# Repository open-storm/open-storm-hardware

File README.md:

# open-storm-hardware
Schematics for open storm hardware.

## perfect cell
**[perfect-cell]** contains Eagle schematics for the _perfect-cell_ board. This board is intended for use with the [perfect-cell](https://github.com/open-storm/perfect-cell) firmware. This board features:

- Cypress CY8C5888LTI-LP097 Programmable System-on-Chip
- Cortex M3 32-bit ARM processor
- 64 KB SRAM
- 256 KB Flash
- Support for Telit cellular modules
- 40 I/O pins for sensors and actuators

## level shifter and relay board
**[level-shifter]** contains Eagle schematics for a level shifter and relay board that can be used to interface the _perfect-cell_ board with higher voltage equipment (such as a valve or autosampler).

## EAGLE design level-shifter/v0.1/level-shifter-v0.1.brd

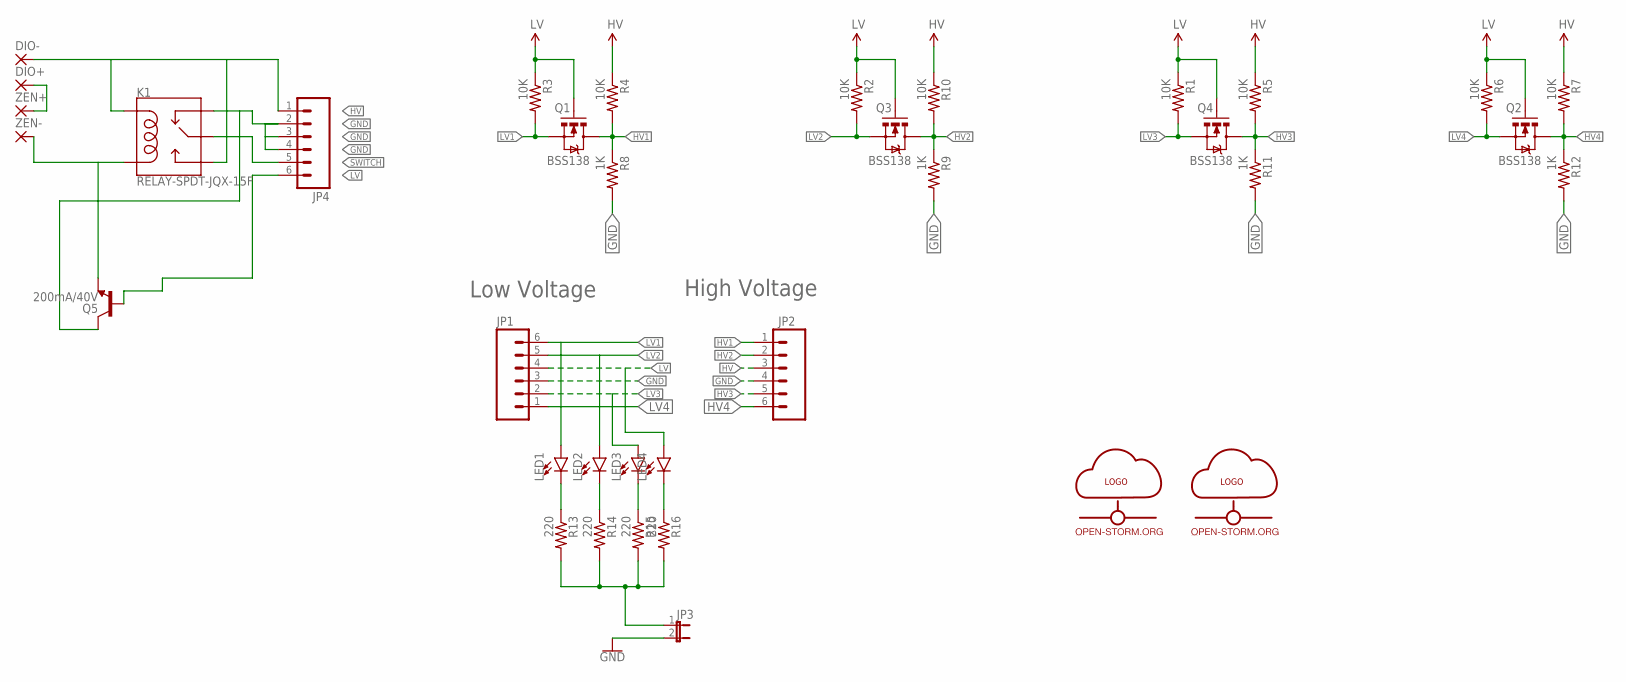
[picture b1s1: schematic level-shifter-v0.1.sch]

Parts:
DIO+: 2,15/1,0
DIO-: 2,15/1,0
JP1, JP2, JP4: M06SIP; 1X06
JP3: JUMPER-2PTH; 1X02
K1: RELAY-SPDT-JQX-15F; RELAY-T90
LED1, LED2, LED3, LED4: LED5MM; LED_5MM
Q1, Q2, Q3, Q4: BSS138; TO-92
Q5: 200mA/40V; TO-92
R1, R2, R3, R4, R5, R6, R7, R10: 10K; AXIAL-0.4
R8, R9, R11, R12: 1K; AXIAL-0.4
R13, R14, R15, R16: 220; AXIAL-0.4
U$1: OPEN-STORM-LOGO
U$2: OPEN-STORM-LOGO-SMALL
ZEN+: 2,15/1,0
ZEN-: 2,15/1,0

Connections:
GND: JP1.3, JP2.4, JP3.2, JP4.2, JP4.3, JP4.4, K1.NC, Q5.3 (C), R8.P$2 (2), R9.P$2 (2), R11.P$2 (2), R12.P$2 (2)
HV: DIO-.1, JP2.3, JP4.1, K1.COIL1, K1.NO, R4.P$1 (1), R5.P$1 (1), R7.P$1 (1), R10.P$1 (1)
HV1: JP2.1, Q1.1 (D), R4.P$2 (2), R8.P$1 (1)
HV2: JP2.2, Q3.1 (D), R9.P$1 (1), R10.P$2 (2)
HV3: JP2.5, Q4.1 (D), R5.P$2 (2), R11.P$1 (1)
HV4: JP2.6, Q2.1 (D), R7.P$2 (2), R12.P$1 (1)
LV: JP1.4, JP4.6, LED4.A, Q1.3 (G), Q2.3 (G), Q3.3 (G), Q4.3 (G), Q5.2 (B), R1.P$1 (1), R2.P$1 (1), R3.P$1 (1), R6.P$1 (1)
LV1: JP1.6, LED1.A, Q1.2 (S), R3.P$2 (2)
LV2: JP1.5, LED2.A, Q3.2 (S), R2.P$2 (2)
LV3: JP1.2, LED3.A, Q4.2 (S), R1.P$2 (2)
LV4: JP1.1, Q2.2 (S), R6.P$2 (2)
unnamed: DIO+.1, ZEN+.1
unnamed: LED4.K (C), R16.P$1 (1)
unnamed: LED2.K (C), R14.P$1 (1)
unnamed: K1.COIL2, Q5.1 (E), ZEN-.1
unnamed: LED1.K (C), R13.P$1 (1)
unnamed: LED3.K (C), R15.P$1 (1)
unnamed: JP3.1, R13.P$2 (2), R14.P$2 (2), R15.P$2 (2), R16.P$2 (2)
SWITCH: JP4.5, K1.MAIN

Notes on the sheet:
High Voltage
Low Voltage

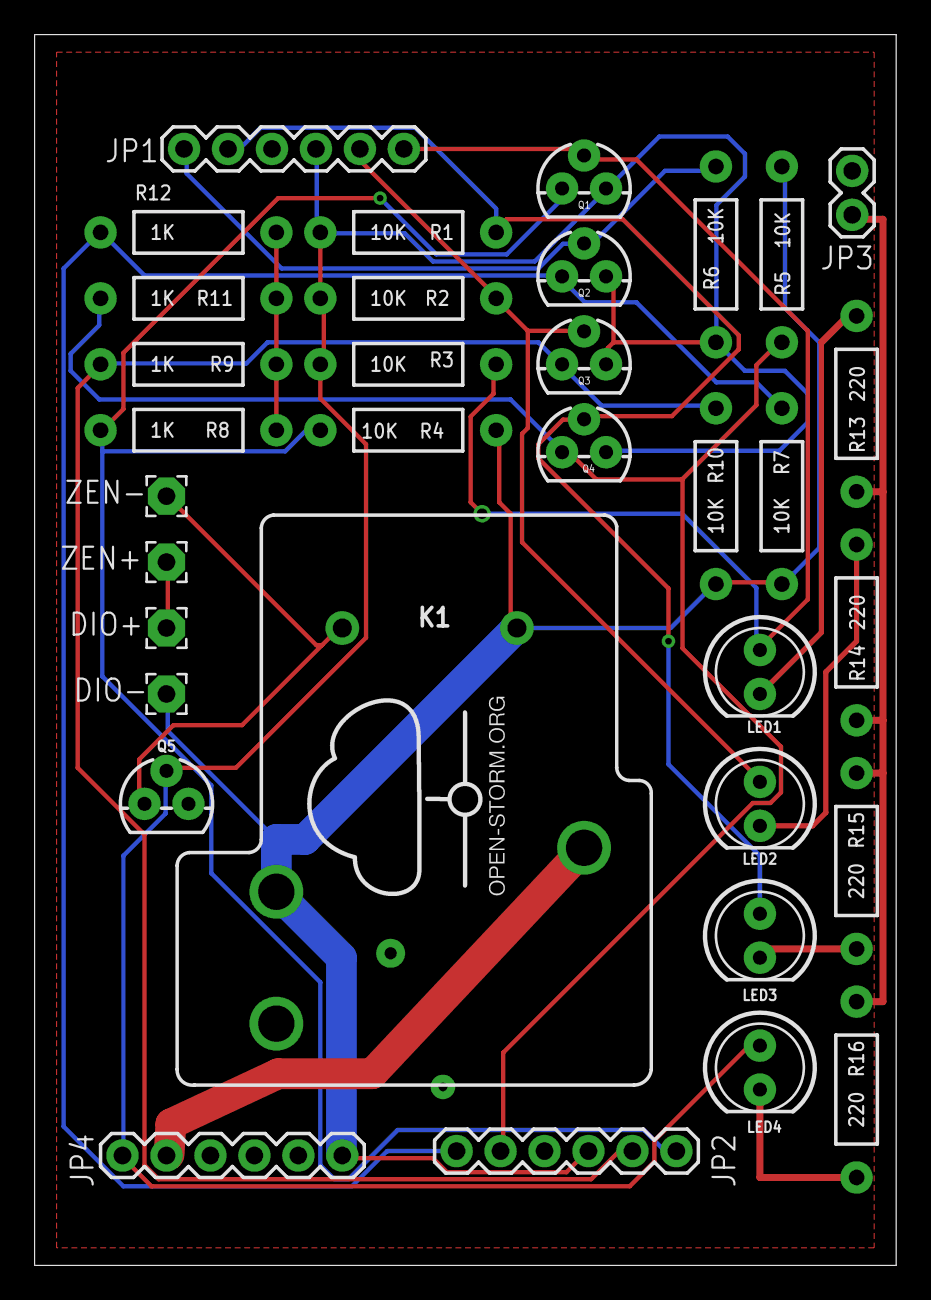
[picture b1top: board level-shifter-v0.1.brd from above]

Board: 2 copper layers, 49.8 x 71.1 mm, 36 parts (1 on the bottom side), 19 nets.

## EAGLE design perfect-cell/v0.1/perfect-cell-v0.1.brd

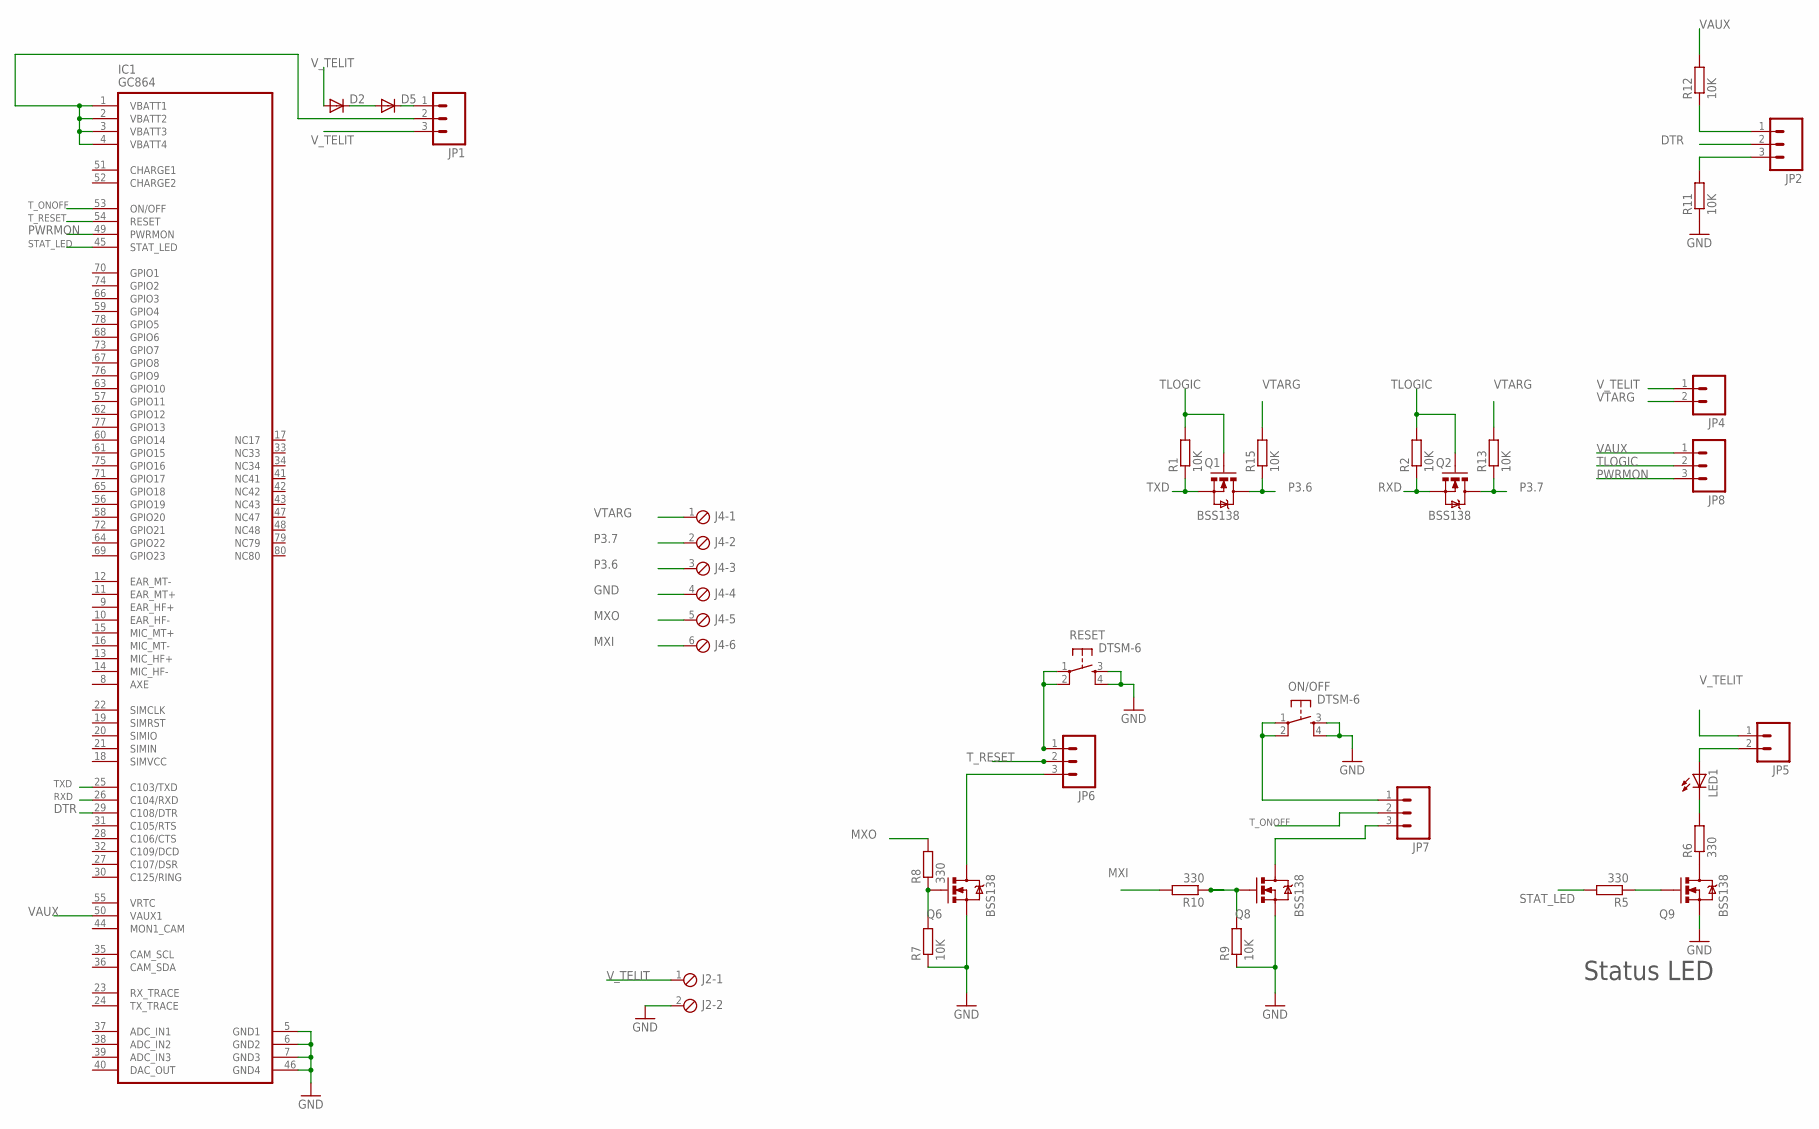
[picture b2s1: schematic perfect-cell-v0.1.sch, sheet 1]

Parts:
D2, D5: DIODESMA; SMA-DIODE
IC1: GC864
J2: MPT2; 2POL254
J4: MPT6; 6POL254
JP1, JP2, JP6, JP7, JP8: M03LOCK; 1X03_LOCK
JP4, JP5: M02LOCK; 1X02_LOCK
LED1: LEDSML0805; SML0805
ON/OFF: DTSM-6
Q1, Q2, Q6, Q8, Q9: BSS138; SOT23-3
R1, R2, R7, R9, R11, R12, R13, R15: 10K; R0805
R5, R6, R8, R10: 330; R0805
RESET: DTSM-6

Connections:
CHARGE1: IC1.51 (CHARGE1)
CHARGE2: IC1.52 (CHARGE2)
DTR: IC1.29 (C108/DTR), JP2.2
GND: IC1.5 (GND1), IC1.6 (GND2), IC1.7 (GND3), IC1.46 (GND4), J2.2, J4.4, ON/OFF.3, ON/OFF.4, Q6.2 (S), Q8.2 (S), Q9.2 (S), R7.1, R9.1, R11.1, RESET.3, RESET.4; also elsewhere on the board
MXI: J4.6, R10.2; also elsewhere on the board
MXO: J4.5, R8.2; also elsewhere on the board
unnamed: Q6.1 (G), R7.2, R8.1
unnamed: IC1.1 (VBATT1), IC1.2 (VBATT2), IC1.3 (VBATT3), IC1.4 (VBATT4), JP1.2
unnamed: D2.C, D5.A
unnamed: Q9.3 (D), R6.1
unnamed: JP5.2, LED1.A
unnamed: LED1.C, R6.2
unnamed: Q8.1 (G), R9.2, R10.1
unnamed: Q9.1 (G), R5.1
unnamed: JP2.1, R12.1
unnamed: JP2.3, R11.2
unnamed: D5.C, JP1.1
unnamed: JP7.3, Q8.3 (D)
unnamed: JP6.3, Q6.3 (D)
unnamed: JP7.1, ON/OFF.1, ON/OFF.2
unnamed: JP6.1, RESET.1, RESET.2
P3.6: J4.3, Q1.3 (D), R15.1; also elsewhere on the board
P3.7: J4.2, Q2.3 (D), R13.1; also elsewhere on the board
PWRMON: IC1.49 (PWRMON), JP8.3
RXD: IC1.26 (C104/RXD), Q2.2 (S), R2.1
STAT_LED: IC1.45 (STAT_LED), R5.2
TLOGIC: JP8.2, Q1.1 (G), Q2.1 (G), R1.2, R2.2
TXD: IC1.25 (C103/TXD), Q1.2 (S), R1.1
T_ONOFF: IC1.53 (ON/OFF), JP7.2
T_RESET: IC1.54 (RESET), JP6.2
VAUX: IC1.50 (VAUX1), JP8.1, R12.2
VTARG: J4.1, JP4.2, R13.2, R15.2
V_TELIT: D2.A, J2.1, JP1.3, JP4.1, JP5.1; also elsewhere on the board

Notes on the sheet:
Status LED

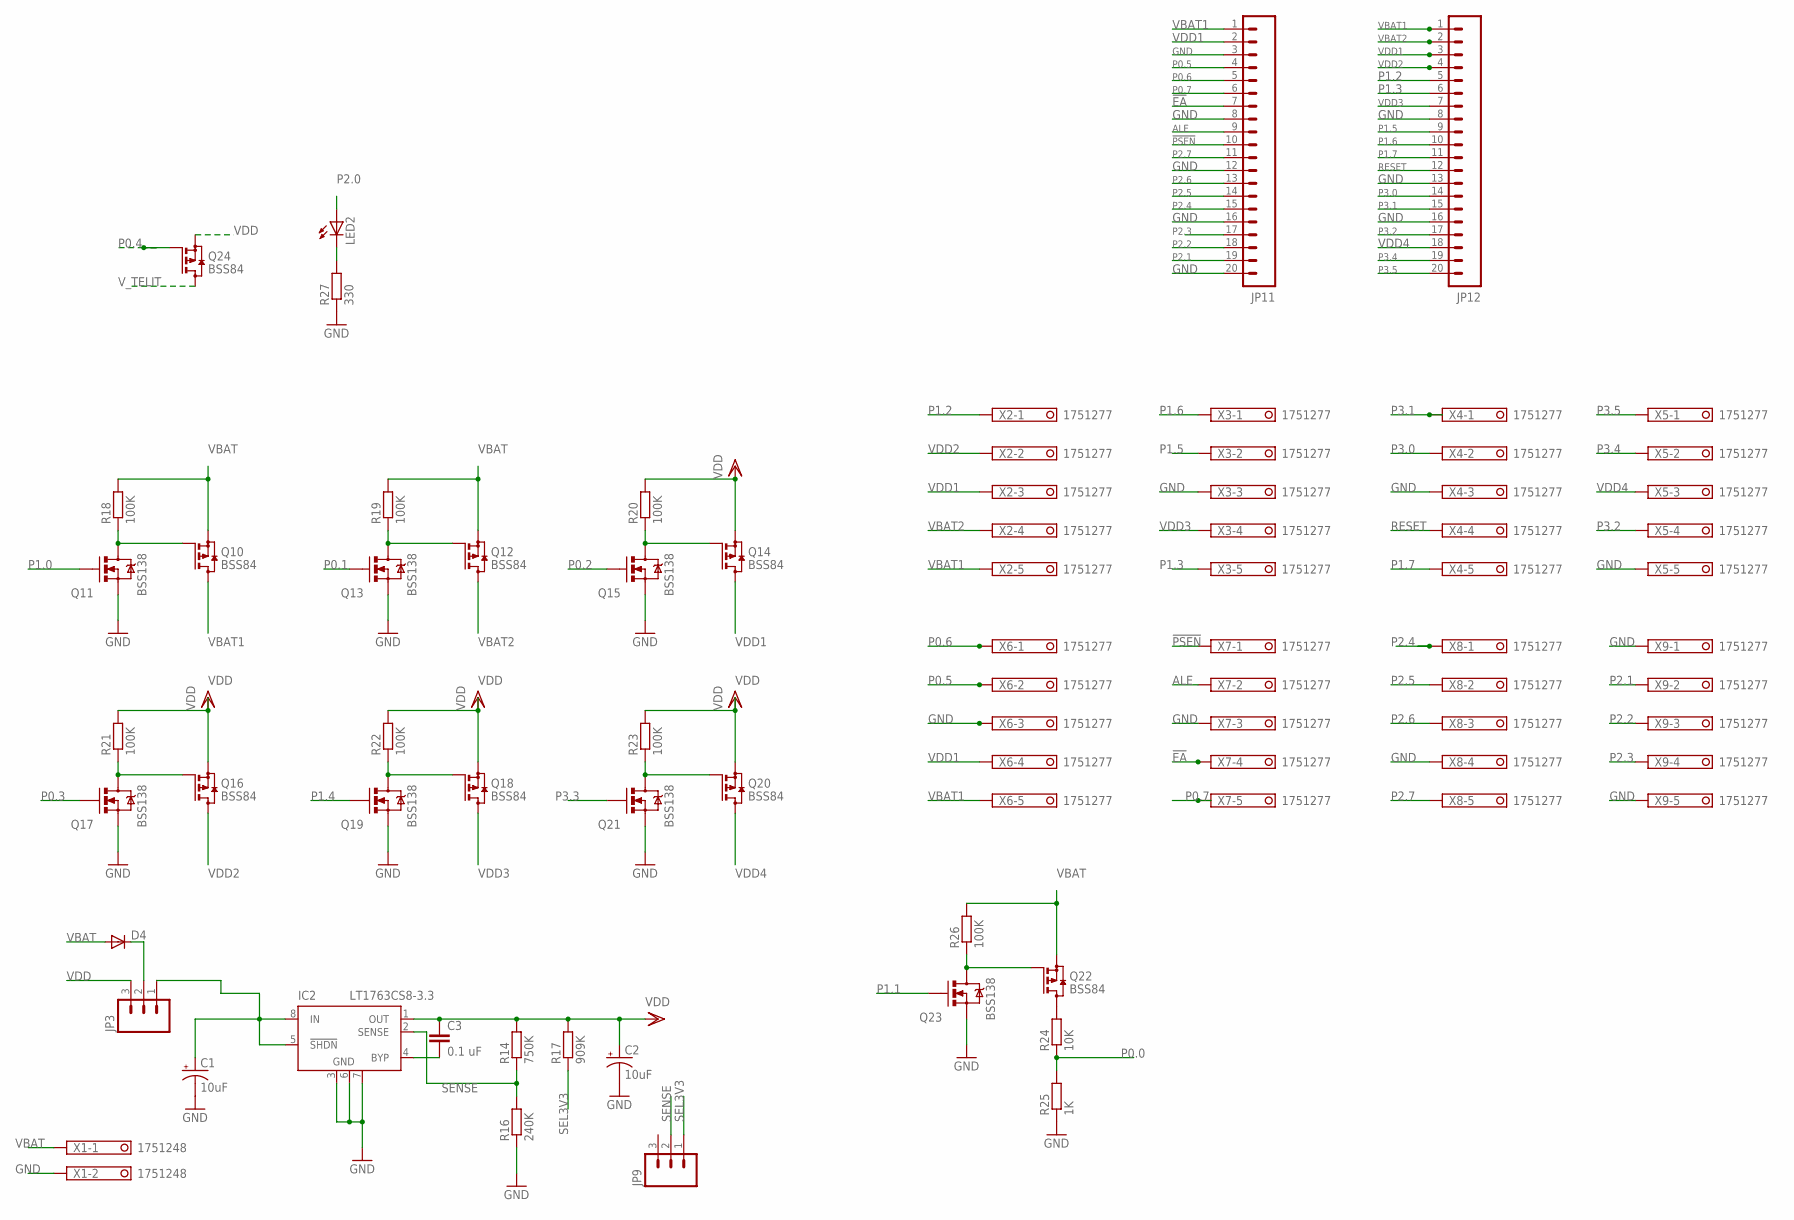
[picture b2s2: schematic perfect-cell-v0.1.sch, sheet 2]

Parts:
C1, C2: 10uF; EIA3216
C3: 0.1 uF; 0402-CAP
D4: DIODESMA; SMA-DIODE
IC2: LT1763CS8-3.3; SOIC8
JP3, JP9: M03LOCK; 1X03_LOCK
JP11, JP12: M20; 1X20
LED2: LEDSML0805; SML0805
Q10, Q12, Q14, Q16, Q18, Q20, Q22, Q24: BSS84; SOT23
Q11, Q13, Q15, Q17, Q19, Q21, Q23: BSS138; SOT23-3
R14: 750K; R0805
R16: 240K; R0805
R17: 909K; R0805
R18, R19, R20, R21, R22, R23, R26: 100K; R0805
R24: 10K; R0805
R25: 1K; R0805
R27: 330; R0805
X1: 1751248
X2, X3, X4, X5, X6, X7, X8, X9: 1751277

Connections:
!EA: JP11.7, X7.4; also elsewhere on the board
!PSEN: JP11.10, X7.1; also elsewhere on the board
ALE: JP11.9, X7.2; also elsewhere on the board
GND: C1.C (-), C2.C (-), IC2.3 (GND), IC2.6 (GND), IC2.7 (GND), JP11.3, JP11.8, JP11.12, JP11.16, JP11.20, JP12.8, JP12.13, JP12.16, Q11.2 (S), Q13.2 (S), Q15.2 (S), Q17.2 (S), Q19.2 (S), Q21.2 (S), Q23.2 (S), R16.1, R25.1, R27.1, X1.2, X3.3, X4.3, X5.5, X6.3, X7.3, X8.4, X9.1, X9.5; also elsewhere on the board
unnamed: D4.C, JP3.2
unnamed: Q10.1 (G), Q11.3 (D), R18.1
unnamed: C1.A (+), IC2.5 (!SHDN), IC2.8 (IN), JP3.1
unnamed: Q12.1 (G), Q13.3 (D), R19.1
unnamed: C3.2, IC2.4 (BYP)
unnamed: Q14.1 (G), Q15.3 (D), R20.1
unnamed: Q16.1 (G), Q17.3 (D), R21.1
unnamed: Q18.1 (G), Q19.3 (D), R22.1
unnamed: Q20.1 (G), Q21.3 (D), R23.1
unnamed: Q22.1 (G), Q23.3 (D), R26.1
unnamed: Q22.3 (D), R24.2
unnamed: LED2.C, R27.2
P0.0: R24.1, R25.2; also elsewhere on the board
P0.1: Q13.1 (G); also elsewhere on the board
P0.2: Q15.1 (G); also elsewhere on the board
P0.3: Q17.1 (G); also elsewhere on the board
P0.4: Q24.1 (G); also elsewhere on the board
P0.5: JP11.4, X6.2; also elsewhere on the board
P0.6: JP11.5, X6.1; also elsewhere on the board
P0.7: JP11.6, X7.5; also elsewhere on the board
P1.0: Q11.1 (G); also elsewhere on the board
P1.1: Q23.1 (G); also elsewhere on the board
P1.2: JP12.5, X2.1; also elsewhere on the board
P1.3: JP12.6, X3.5; also elsewhere on the board
P1.4: Q19.1 (G); also elsewhere on the board
P1.5: JP12.9, X3.2; also elsewhere on the board
P1.6: JP12.10, X3.1; also elsewhere on the board
P1.7: JP12.11, X4.5; also elsewhere on the board
P2.0: LED2.A; also elsewhere on the board
P2.1: JP11.19, X9.2; also elsewhere on the board
P2.2: JP11.18, X9.3; also elsewhere on the board
P2.3: JP11.17, X9.4; also elsewhere on the board
P2.4: JP11.15, X8.1; also elsewhere on the board
P2.5: JP11.14, X8.2; also elsewhere on the board
P2.6: JP11.13, X8.3; also elsewhere on the board
P2.7: JP11.11, X8.5; also elsewhere on the board
P3.0: JP12.14, X4.2; also elsewhere on the board
P3.1: JP12.15, X4.1; also elsewhere on the board
P3.2: JP12.17, X5.4; also elsewhere on the board
P3.3: Q21.1 (G); also elsewhere on the board
P3.4: JP12.19, X5.2; also elsewhere on the board
P3.5: JP12.20, X5.1; also elsewhere on the board
RESET: JP12.12, X4.4; also elsewhere on the board
SEL3V3: JP9.1, R17.1
SENSE: IC2.2 (SENSE), JP9.2, R14.1, R16.2
VBAT: D4.A, Q10.2 (S), Q12.2 (S), Q22.2 (S), R18.2, R19.2, R26.2, X1.1
VBAT1: JP11.1, JP12.1, Q10.3 (D), X2.5, X6.5
VBAT2: JP12.2, Q12.3 (D), X2.4
VDD: C2.A (+), C3.1, IC2.1 (OUT), JP3.3, Q14.2 (S), Q16.2 (S), Q18.2 (S), Q20.2 (S), Q24.2 (S), R14.2, R17.2, R20.2, R21.2, R22.2, R23.2; also elsewhere on the board
VDD1: JP11.2, JP12.3, Q14.3 (D), X2.3, X6.4
VDD2: JP12.4, Q16.3 (D), X2.2
VDD3: JP12.7, Q18.3 (D), X3.4
VDD4: JP12.18, Q20.3 (D), X5.3
V_TELIT: Q24.3 (D); also elsewhere on the board

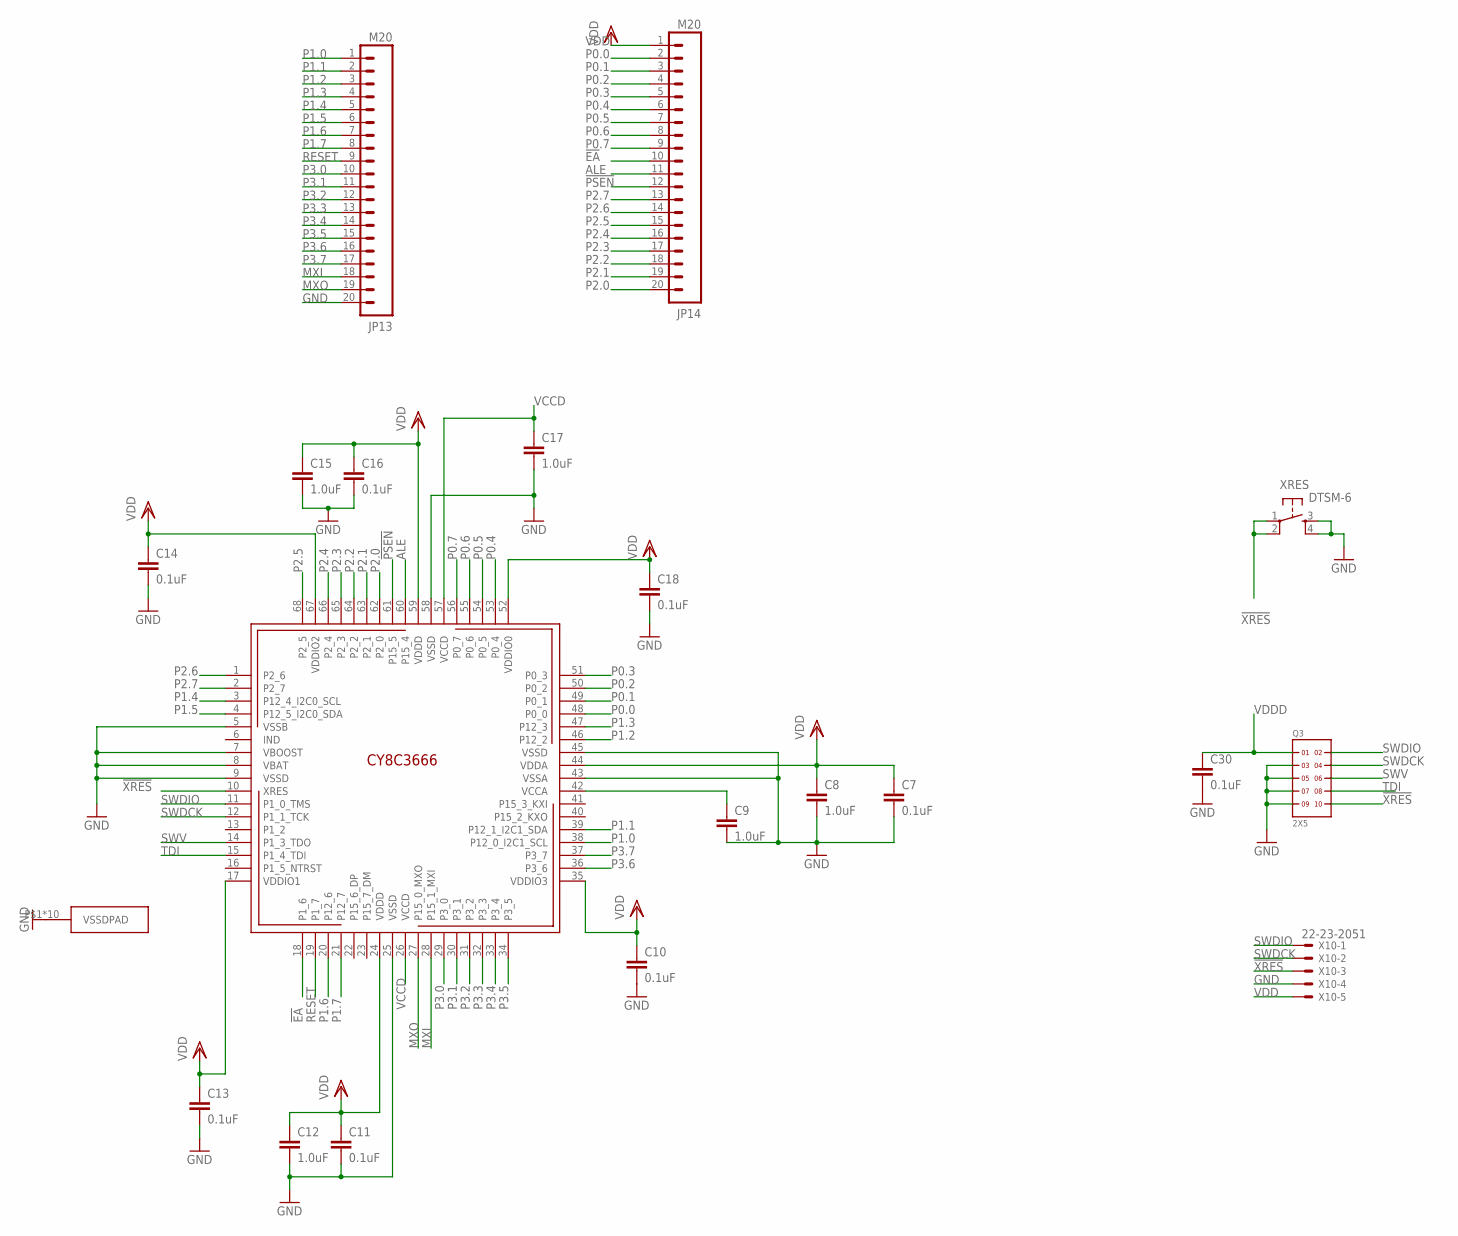
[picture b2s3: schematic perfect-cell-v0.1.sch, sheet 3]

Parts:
C7, C10, C11, C13, C14, C16, C18, C30: 0.1uF; 0402-CAP
C8, C9, C12, C15, C17: 1.0uF; 0402-CAP
JP13, JP14: M20; 1X20
Q3: 2X5; FTSH-105-01-XXX-DV-K
U$1: CY8C3X66LTI; QFN-68
X10: 22-23-2051
XRES: DTSM-6

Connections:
!EA: JP14.10, U$1.18 (P1_6); also elsewhere on the board
!PSEN: JP14.12, U$1.61 (P15_5); also elsewhere on the board
!XRES: Q3.10, U$1.10 (XRES), X10.3, XRES.1, XRES.2
ALE: JP14.11, U$1.60 (P15_4); also elsewhere on the board
GND: C7.2, C8.2, C9.2, C10.2, C11.2, C12.2, C13.2, C14.2, C15.2, C16.2, C17.2, C18.2, C30.2, JP13.20, Q3.3, Q3.5, Q3.7, Q3.9, U$1.5 (VSSB), U$1.7 (VBOOST), U$1.8 (VBAT), U$1.9 (VSSD), U$1.25 (VSSD), U$1.43 (VSSA), U$1.45 (VSSD), U$1.58 (VSSD), U$1.P$1 (VSSDPAD), U$1.P$2 (VSSDPAD), U$1.P$3 (VSSDPAD), U$1.P$4 (VSSDPAD), U$1.P$5 (VSSDPAD), U$1.P$6 (VSSDPAD), U$1.P$7 (VSSDPAD), U$1.P$8 (VSSDPAD), U$1.P$9 (VSSDPAD), U$1.PAD (VSSDPAD), X10.4, XRES.3, XRES.4; also elsewhere on the board
MXI: JP13.18, U$1.28 (P15_1_MXI); also elsewhere on the board
MXO: JP13.19, U$1.27 (P15_0_MXO); also elsewhere on the board
unnamed: C9.1, U$1.42 (VCCA)
P0.0: JP14.2, U$1.48 (P0_0); also elsewhere on the board
P0.1: JP14.3, U$1.49 (P0_1); also elsewhere on the board
P0.2: JP14.4, U$1.50 (P0_2); also elsewhere on the board
P0.3: JP14.5, U$1.51 (P0_3); also elsewhere on the board
P0.4: JP14.6, U$1.53 (P0_4); also elsewhere on the board
P0.5: JP14.7, U$1.54 (P0_5); also elsewhere on the board
P0.6: JP14.8, U$1.55 (P0_6); also elsewhere on the board
P0.7: JP14.9, U$1.56 (P0_7); also elsewhere on the board
P1.0: JP13.1, U$1.38 (P12_0_I2C1_SCL); also elsewhere on the board
P1.1: JP13.2, U$1.39 (P12_1_I2C1_SDA); also elsewhere on the board
P1.2: JP13.3, U$1.46 (P12_2); also elsewhere on the board
P1.3: JP13.4, U$1.47 (P12_3); also elsewhere on the board
P1.4: JP13.5, U$1.3 (P12_4_I2C0_SCL); also elsewhere on the board
P1.5: JP13.6, U$1.4 (P12_5_I2C0_SDA); also elsewhere on the board
P1.6: JP13.7, U$1.20 (P12_6); also elsewhere on the board
P1.7: JP13.8, U$1.21 (P12_7); also elsewhere on the board
P2.0: JP14.20, U$1.62 (P2_0); also elsewhere on the board
P2.1: JP14.19, U$1.63 (P2_1); also elsewhere on the board
P2.2: JP14.18, U$1.64 (P2_2); also elsewhere on the board
P2.3: JP14.17, U$1.65 (P2_3); also elsewhere on the board
P2.4: JP14.16, U$1.66 (P2_4); also elsewhere on the board
P2.5: JP14.15, U$1.68 (P2_5); also elsewhere on the board
P2.6: JP14.14, U$1.1 (P2_6); also elsewhere on the board
P2.7: JP14.13, U$1.2 (P2_7); also elsewhere on the board
P3.0: JP13.10, U$1.29 (P3_0); also elsewhere on the board
P3.1: JP13.11, U$1.30 (P3_1); also elsewhere on the board
P3.2: JP13.12, U$1.31 (P3_2); also elsewhere on the board
P3.3: JP13.13, U$1.32 (P3_3); also elsewhere on the board
P3.4: JP13.14, U$1.33 (P3_4); also elsewhere on the board
P3.5: JP13.15, U$1.34 (P3_5); also elsewhere on the board
P3.6: JP13.16, U$1.36 (P3_6); also elsewhere on the board
P3.7: JP13.17, U$1.37 (P3_7); also elsewhere on the board
RESET: JP13.9, U$1.19 (P1_7); also elsewhere on the board
SWDCK: Q3.4, U$1.12 (P1_1_TCK), X10.2
SWDIO: Q3.2, U$1.11 (P1_0_TMS), X10.1
SWV: Q3.6, U$1.14 (P1_3_TDO)
TDI: Q3.8, U$1.15 (P1_4_TDI)
VCCD: C17.1, U$1.26 (VCCD), U$1.57 (VCCD)
VDD: C7.1, C8.1, C10.1, C11.1, C12.1, C13.1, C14.1, C15.1, C16.1, C18.1, JP14.1, U$1.17 (VDDIO1), U$1.24 (VDDD), U$1.35 (VDDIO3), U$1.44 (VDDA), U$1.52 (VDDIO0), U$1.59 (VDDD), U$1.67 (VDDIO2), X10.5; also elsewhere on the board
VDDD: C30.1, Q3.1

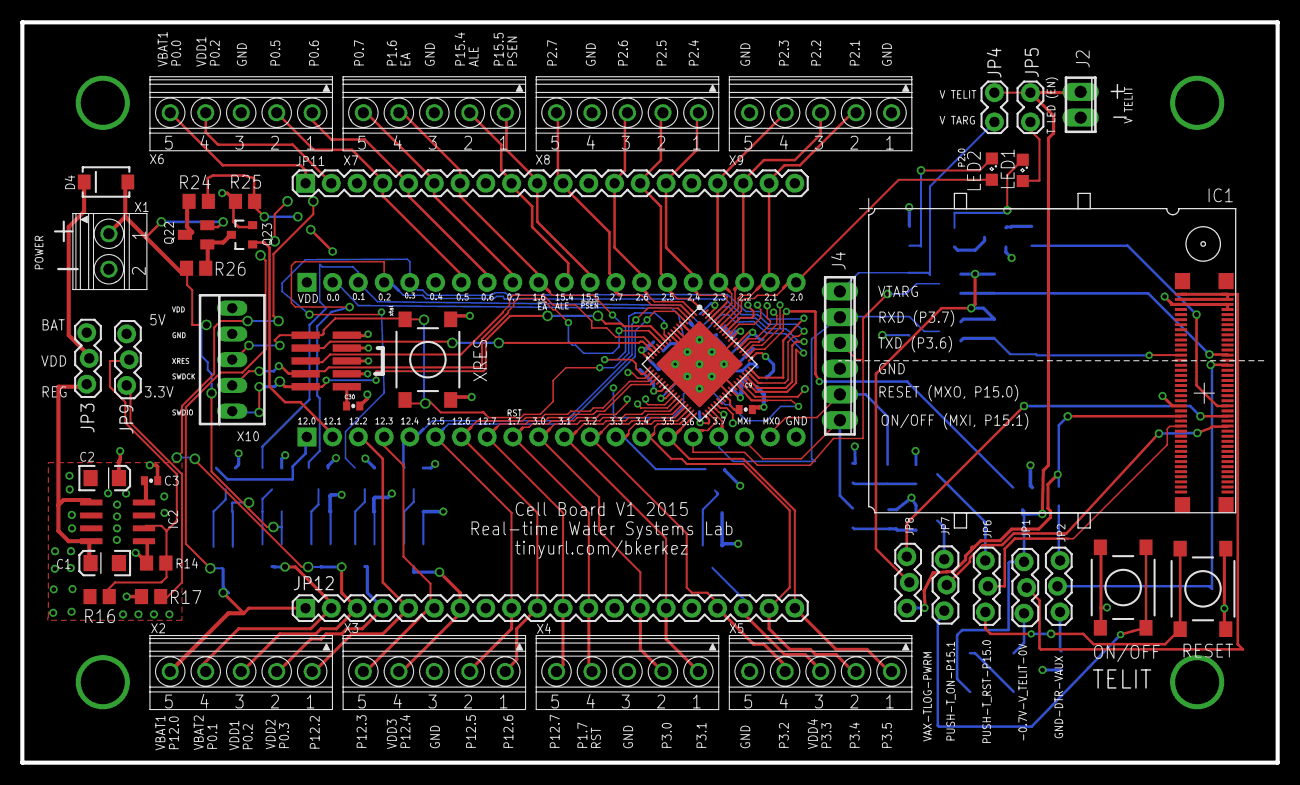
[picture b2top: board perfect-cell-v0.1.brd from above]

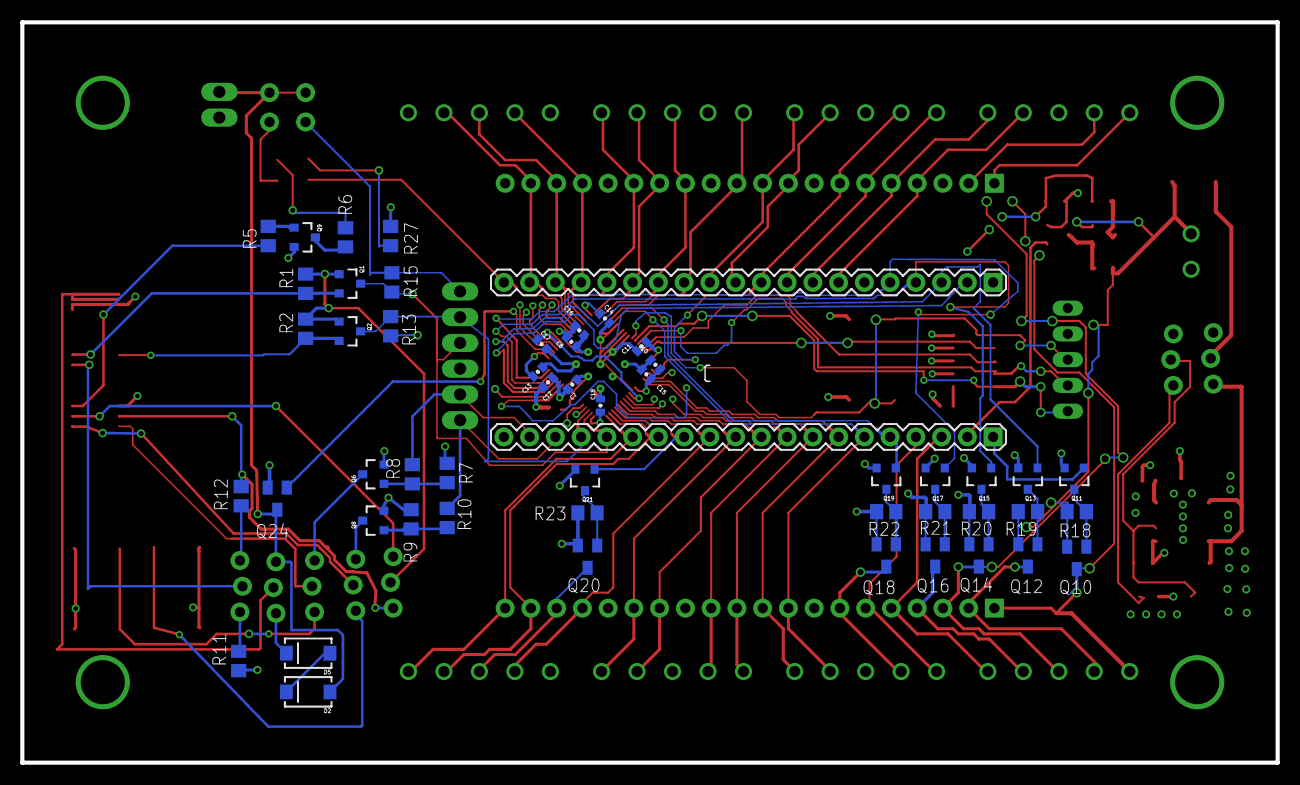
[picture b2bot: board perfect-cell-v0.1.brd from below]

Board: 4 copper layers, 123.8 x 73.0 mm, 98 parts (52 on the bottom side), 95 nets.

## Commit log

2017-06-01 Initial commit of perfect-cell-v0.1
2017-08-31 Add level shifter board
2017-08-31 Add level shifter image and description

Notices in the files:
parts and their libraries:
SparkFun-Electromechanical: Licensing: Creative Commons ShareAlike 4.0 International - https://creativecommons.org/licenses/by-sa/4.0
